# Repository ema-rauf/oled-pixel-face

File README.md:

# OLED Pixel Face Display

A small ESP32 board that shows pixel-art faces on a 0.96" OLED screen. Two buttons change the face, put the screen to sleep, and turn on automatic mode, where the face changes by itself every 2.5 seconds.

## How it works

The ESP32 DevKit V1 talks to an SSD1306 OLED over I2C and draws each face from chunky pixel blocks. There are four faces: happy, surprised, sleepy and curious. The awake faces blink at random, and sleep mode shows a closed-eye face with floating "Zzz".

Both buttons connect a GPIO pin to ground, and the firmware turns on the ESP32's internal pull-ups, so no resistors are needed.

| Button | Short press | Hold about 0.7 s |
|---|---|---|
| Next (GPIO25) | Next face, turns automatic mode off | Previous face |
| Sleep (GPIO26) | Sleep or wake | Automatic mode on or off (while awake) |

## Why I made it

I first built this on a breadboard with loose jumper wires. I wanted it on one proper PCB so the screen, buttons and ESP32 are all in one piece and nothing can come loose.

## The PCB

A 60 x 54 mm two-layer carrier board. The ESP32 DevKit V1 (30-pin) plugs into two female headers, the OLED plugs into a 4-pin socket (GND, VCC, SCL, SDA), and the two buttons are on the board. The bottom layer is a ground plane. ERC and DRC in KiCad 9 both report zero violations.

### Pin map

| Function | ESP32 pin |
|---|---|
| OLED SDA | GPIO21 |
| OLED SCL | GPIO22 |
| OLED power | 3V3 |
| OLED ground | GND |
| Next button | GPIO25 |
| Sleep button | GPIO26 |

### Parts

| Part | Qty |
|---|---|
| ESP32 DevKit V1, 30-pin | 1 |
| 1x15 female header, 2.54 mm | 2 |
| 1x4 female header, 2.54 mm | 1 |
| 0.96" SSD1306 128x64 I2C OLED | 1 |
| 6x6 mm tactile switch, through-hole | 2 |
| 100 nF capacitor, 0805 (optional) | 1 |

## Files

- `hardware/` - KiCad 9 project (open `oled_face.kicad_pro`)
- `firmware/oled_face/oled_face.ino` - Arduino sketch
- `images/` - board renders and schematic

## Firmware

Open `firmware/oled_face/oled_face.ino` in the Arduino IDE, install the **Adafruit SSD1306** and **Adafruit GFX Library** libraries, select **ESP32 Dev Module**, and upload.

## Before you build

The board assumes 22.86 mm between the two rows of DevKit header pins, and an OLED module with pins in the order GND, VCC, SCL, SDA. Check both on your own parts first.

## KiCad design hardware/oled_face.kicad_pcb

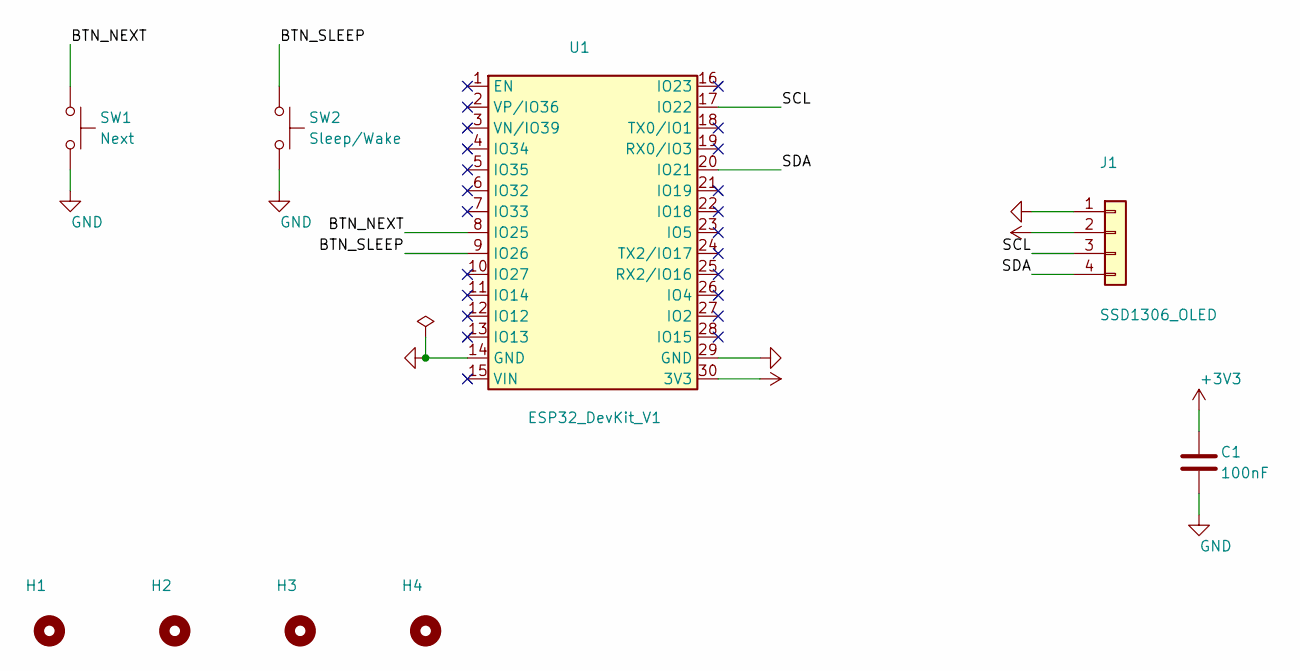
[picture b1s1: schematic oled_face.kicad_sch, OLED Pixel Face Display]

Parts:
C1: 100nF; C_0805_2012Metric
H1, H2, H3, H4: MountingHole_3.2mm; MountingHole_3.2mm_M3
J1: SSD1306_OLED; PinSocket_1x04_P2.54mm_Vertical
SW1: Next; SW_Tactile_6mm_Diagonal
SW2: Sleep/Wake; SW_Tactile_6mm_Diagonal
U1: ESP32_DevKit_V1; ESP32_DevKit_V1_30pin_Socket

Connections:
+3V3: C1.1, J1.2, U1.30 (3V3)
/BTN_NEXT: SW1.1, U1.8 (IO25)
/BTN_SLEEP: SW2.1, U1.9 (IO26)
/SCL: J1.3, U1.17 (IO22)
/SDA: J1.4, U1.20 (IO21)
GND: C1.2, J1.1, SW1.2, SW2.2, U1.14 (GND), U1.29 (GND)

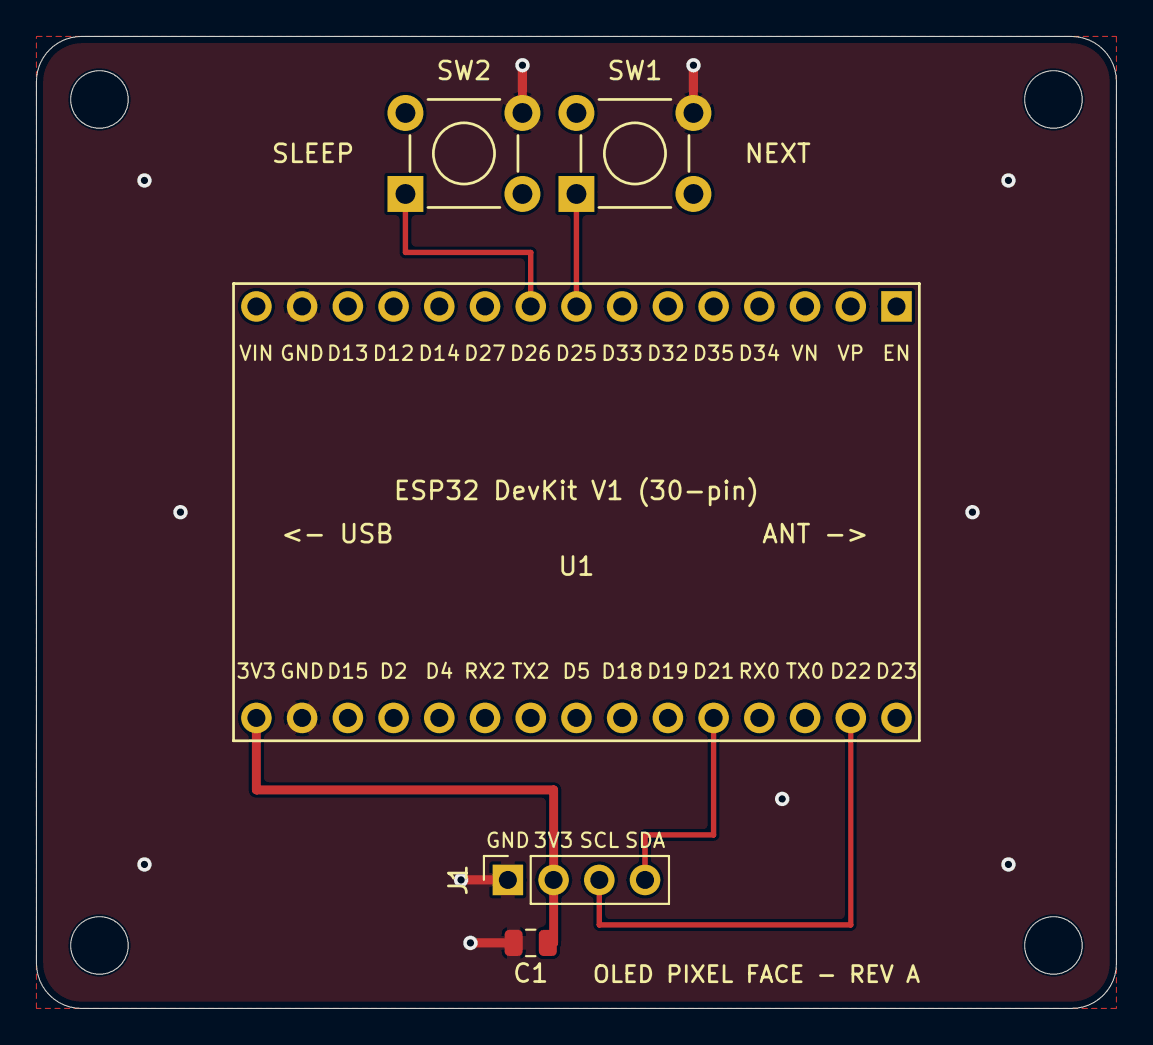
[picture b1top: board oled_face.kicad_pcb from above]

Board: 2 copper layers, 60.0 x 54.0 mm, 9 parts (0 on the bottom side), 6 nets.
